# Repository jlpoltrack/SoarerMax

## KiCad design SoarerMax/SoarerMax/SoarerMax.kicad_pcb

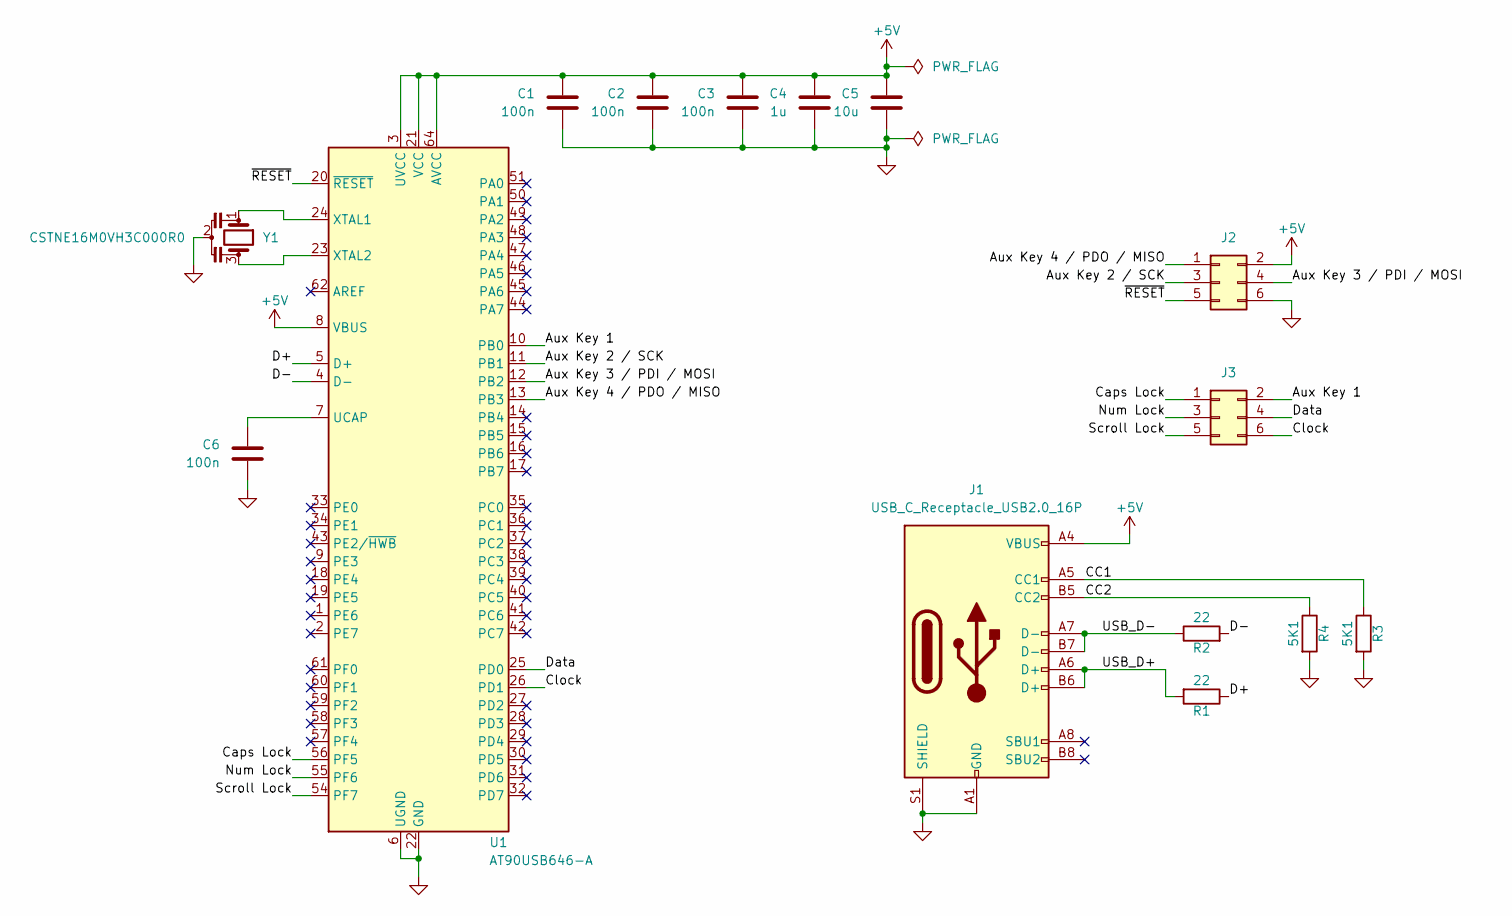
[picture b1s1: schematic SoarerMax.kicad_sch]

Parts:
C1, C2, C3, C6: 100n; C_0603_1608Metric_Pad1.08x0.95mm_HandSolder
C4: 1u; C_0603_1608Metric_Pad1.08x0.95mm_HandSolder
C5: 10u; C_0603_1608Metric_Pad1.08x0.95mm_HandSolder
J1: USB_C_Receptacle_USB2.0_16P; USB_C_Receptacle_GCT_USB4085
J2, J3: Conn_02x03_Odd_Even; PinHeader_2x03_P2.54mm_Vertical
R1, R2: 22; R_0603_1608Metric_Pad0.98x0.95mm_HandSolder
R3, R4: 5K1; R_0603_1608Metric_Pad0.98x0.95mm_HandSolder
U1: AT90USB646-A; TQFP-64_14x14mm_P0.8mm
Y1: CSTNE16M0VH3C000R0; Resonator_SMD_Murata_CSTxExxV-3Pin_3.0x1.1mm

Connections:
+5V: C1.2, C2.2, C3.2, C4.2, C5.2, J1.A4 (VBUS), J1.A9 (VBUS), J1.B4 (VBUS), J1.B9 (VBUS), J2.2, U1.3 (UVCC), U1.8 (VBUS), U1.21 (VCC), U1.52 (VCC), U1.64 (AVCC)
/Aux Key 1: J3.2, U1.10 (PB0)
/Aux Key 2 / SCK: J2.3, U1.11 (PB1)
/Aux Key 3 / PDI / MOSI: J2.4, U1.12 (PB2)
/Aux Key 4 / PDO / MISO: J2.1, U1.13 (PB3)
/CC1: J1.A5 (CC1), R3.1
/CC2: J1.B5 (CC2), R4.1
/Caps Lock: J3.1, U1.56 (PF5)
/Clock: J3.6, U1.26 (PD1)
/D+: R1.1, U1.5 (D+)
/D-: R2.2, U1.4 (D-)
/Data: J3.4, U1.25 (PD0)
/Num Lock: J3.3, U1.55 (PF6)
/Scroll Lock: J3.5, U1.54 (PF7)
/USB_D+: J1.A6 (D+), J1.B6 (D+), R1.2
/USB_D-: J1.A7 (D-), J1.B7 (D-), R2.1
/~RESET: J2.5, U1.20 (~RESET)
GND: C1.1, C2.1, C3.1, C4.1, C5.1, C6.1, J1.A1 (GND), J1.A12 (GND), J1.B1 (GND), J1.B12 (GND), J1.S1 (SHIELD), J2.6, R3.2, R4.2, U1.6 (UGND), U1.22 (GND), U1.53 (GND), U1.63 (GND), Y1.2
unnamed: C6.2, U1.7 (UCAP)
unnamed: U1.24 (XTAL1), Y1.1
unnamed: U1.23 (XTAL2), Y1.3

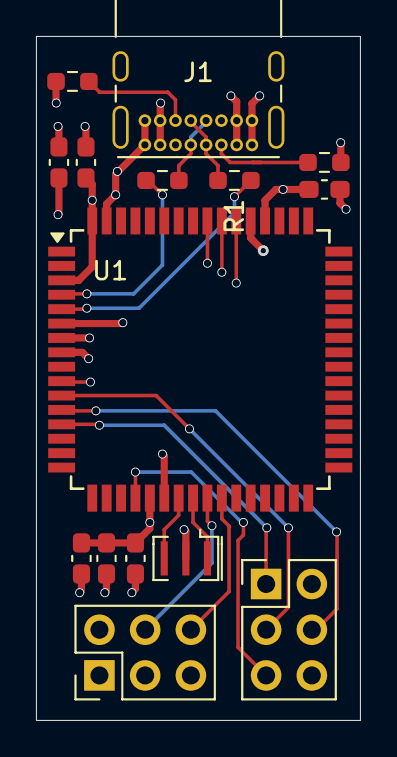
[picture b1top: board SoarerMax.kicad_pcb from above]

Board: 6 copper layers, 18.0 x 38.0 mm, 15 parts (0 on the bottom side), 21 nets.
